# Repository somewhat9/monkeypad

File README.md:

# Monkeypad
Monkeypad is a macropad with 9 switches, an OLED screen and a rotary encoder.

*Completely designed by [@somewhat9](github.com/somewhat9).*  

## Features:
- 128x32 OLED Display
- EC11 Rotary Encoder
- 9 Keys
- 3D Printed Case
- QMK Firmware

### Schematic
Used [KiCAD](https://www.kicad.org/), an open source EDA software, to create the schematic and design the PCB.  

### PCB

### Case
Utilized [Onshape](https://www.onshape.com/en/), a 3D modeling CAD software, to design the 3D models for the case.  

### Firmware
The firmware for this macropad was built using the [QMK](https://qmk.fm/) project.
The open-source repository can be found [here](https://github.com/qmk/qmk_firmware).

## BOM:
- 9x Cherry MX Switches
- 1x EC11 Rotary Encoder
- 1x 128x32 OLED Display
- 1x XIAO RP2040
- 9x Blank DSA Keycaps (White)
- 4x M3x16mm Screws
- 4x M3x5mx4mm Heatset Inserts
- 1x 3D Printed Case

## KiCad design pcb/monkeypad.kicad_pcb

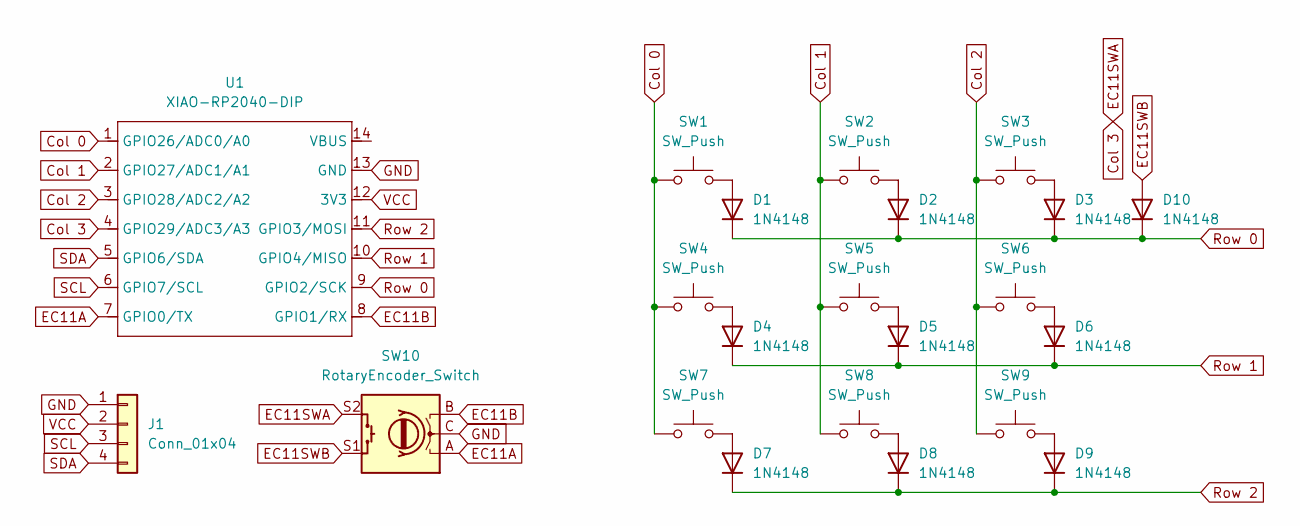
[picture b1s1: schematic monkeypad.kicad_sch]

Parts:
D1, D2, D3, D4, D5, D6, D7, D8, D9, D10: 1N4148; D_DO-35_SOD27_P7.62mm_Horizontal
J1: Conn_01x04; SSD1306-0.91-OLED-4pin-128x32
SW1, SW2, SW3, SW4, SW5, SW6, SW7, SW8, SW9: SW_Push; SW_Cherry_MX_1.00u_PCB
SW10: RotaryEncoder_Switch; RotaryEncoder_Alps_EC11E-Switch_Vertical_H20mm
U1: XIAO-RP2040-DIP

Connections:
Col 0: SW1.1, SW4.1, SW7.1, U1.1 (GPIO26/ADC0/A0)
Col 1: SW2.1, SW5.1, SW8.1, U1.2 (GPIO27/ADC1/A1)
Col 2: SW3.1, SW6.1, SW9.1, U1.3 (GPIO28/ADC2/A2)
Col 3: SW10.S2, U1.4 (GPIO29/ADC3/A3)
EC11A: SW10.A, U1.7 (GPIO0/TX)
EC11B: SW10.B, U1.8 (GPIO1/RX)
EC11SWB: D10.2 (A), SW10.S1
GND: J1.1, SW10.C, U1.13 (GND)
unnamed: D1.2 (A), SW1.2
unnamed: D2.2 (A), SW2.2
unnamed: D3.2 (A), SW3.2
unnamed: D4.2 (A), SW4.2
unnamed: D5.2 (A), SW5.2
unnamed: D6.2 (A), SW6.2
unnamed: D7.2 (A), SW7.2
unnamed: D8.2 (A), SW8.2
unnamed: D9.2 (A), SW9.2
Row 0: D1.1 (K), D2.1 (K), D3.1 (K), D10.1 (K), U1.9 (GPIO2/SCK)
Row 1: D4.1 (K), D5.1 (K), D6.1 (K), U1.10 (GPIO4/MISO)
Row 2: D7.1 (K), D8.1 (K), D9.1 (K), U1.11 (GPIO3/MOSI)
SCL: J1.3, U1.6 (GPIO7/SCL)
SDA: J1.4, U1.5 (GPIO6/SDA)
VCC: J1.2, U1.12 (3V3)

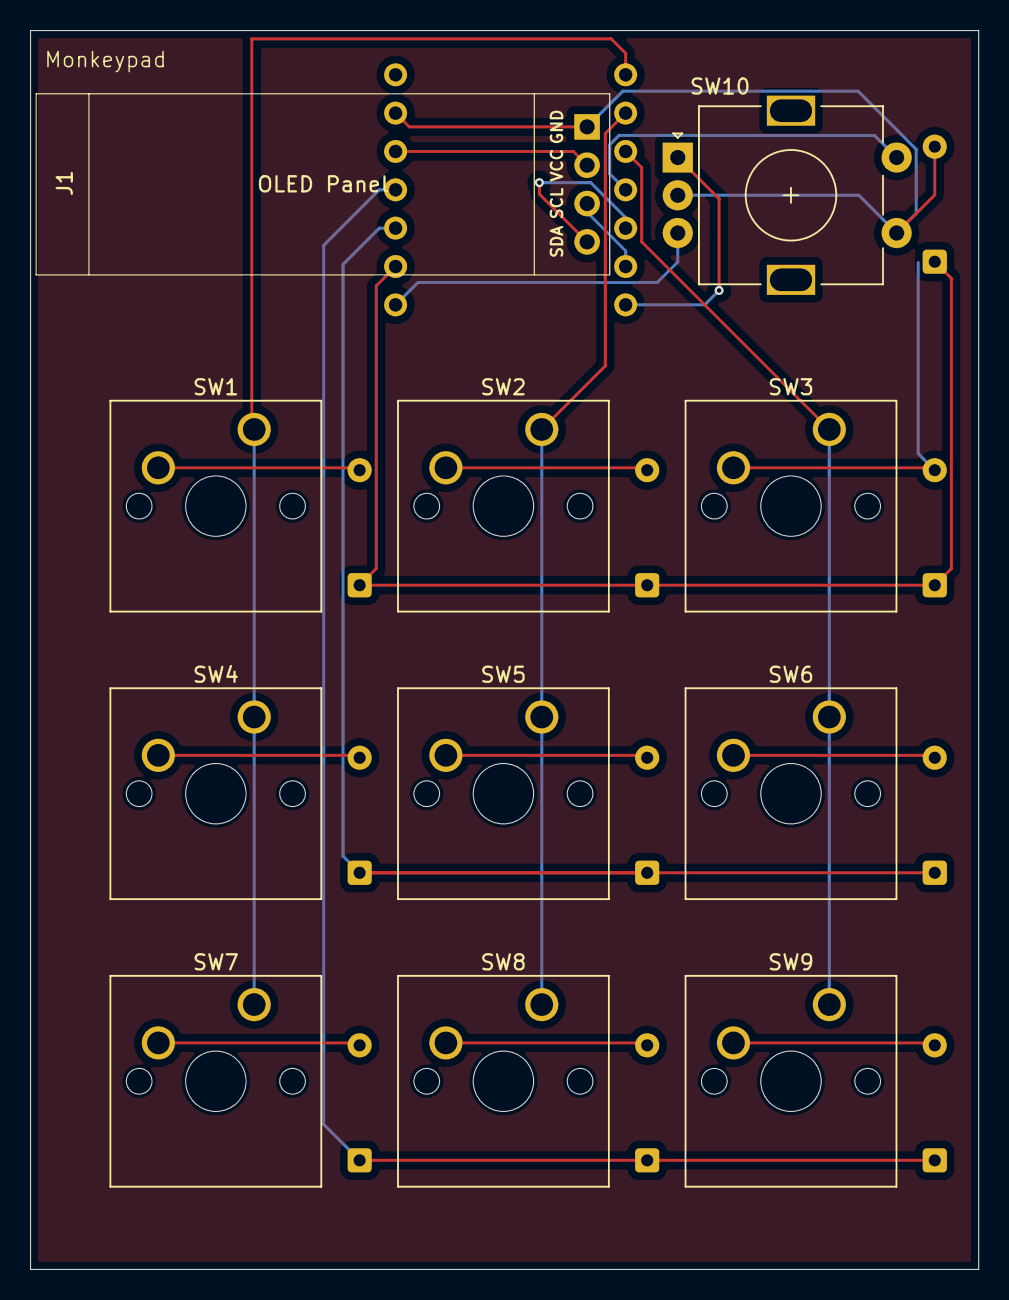
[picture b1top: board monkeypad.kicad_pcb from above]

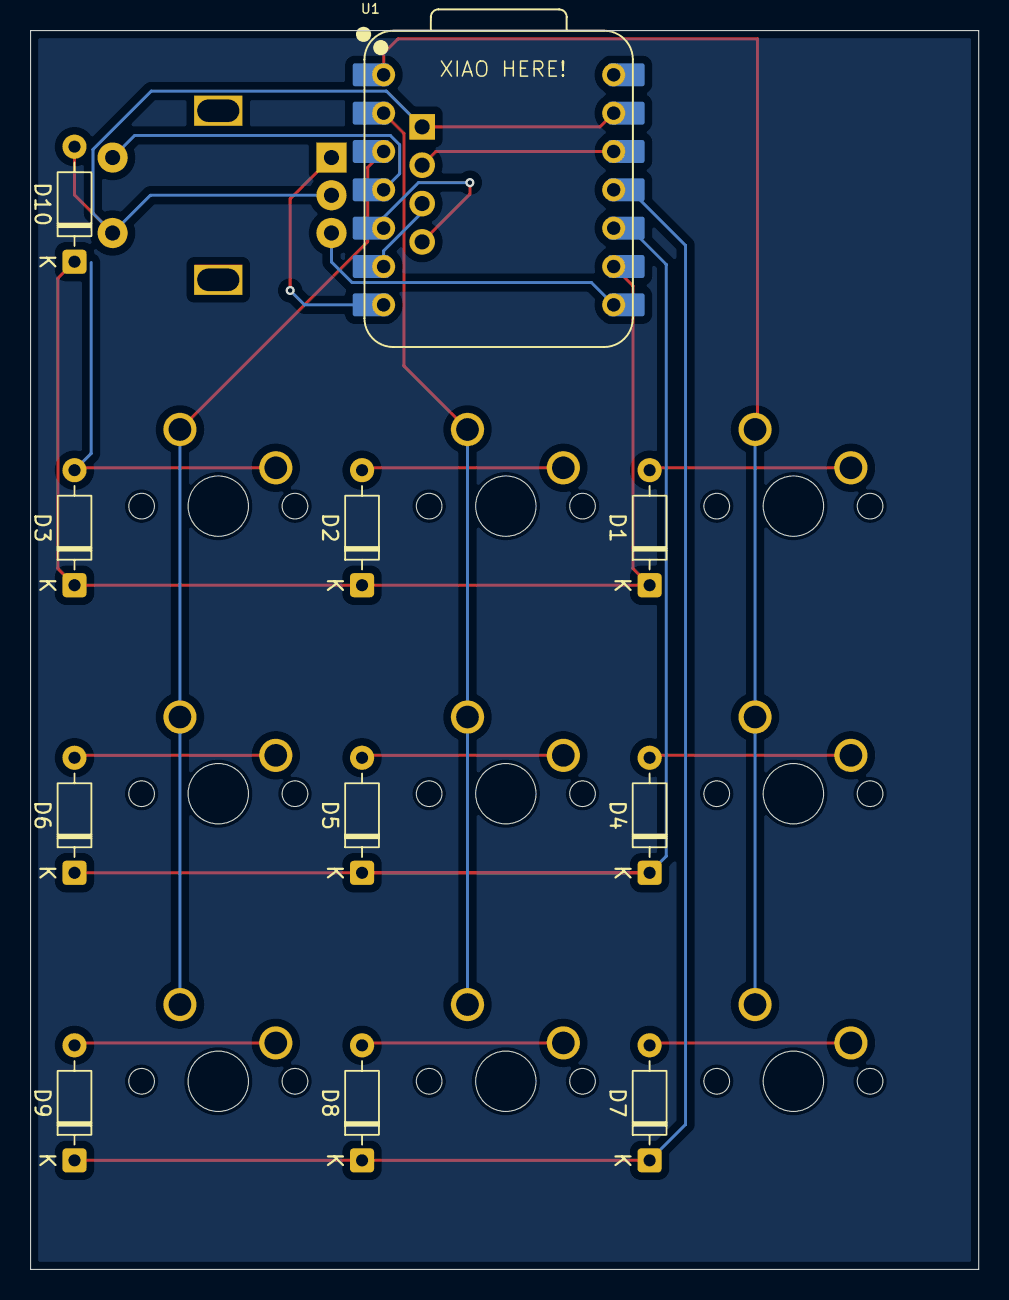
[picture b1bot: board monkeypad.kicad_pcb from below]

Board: 2 copper layers, 62.8 x 82.1 mm, 22 parts (11 on the bottom side), 23 nets.

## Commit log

2025-06-07 Add CAD, PCB, Firmware
    Added all the CAD, PCB and firmware files for the macropad.
2025-06-08 Added 3D Models, Assets, README
    Added 3D models for the PCB, image assets, and a README.
2025-06-08 Updated README
    Fixed formatting issues in README.
2025-06-08 Added Image to README
    Added the monkeypad image to the README.
2025-06-08 Fix README Image
2025-06-08 Fixed Schematic Asset
